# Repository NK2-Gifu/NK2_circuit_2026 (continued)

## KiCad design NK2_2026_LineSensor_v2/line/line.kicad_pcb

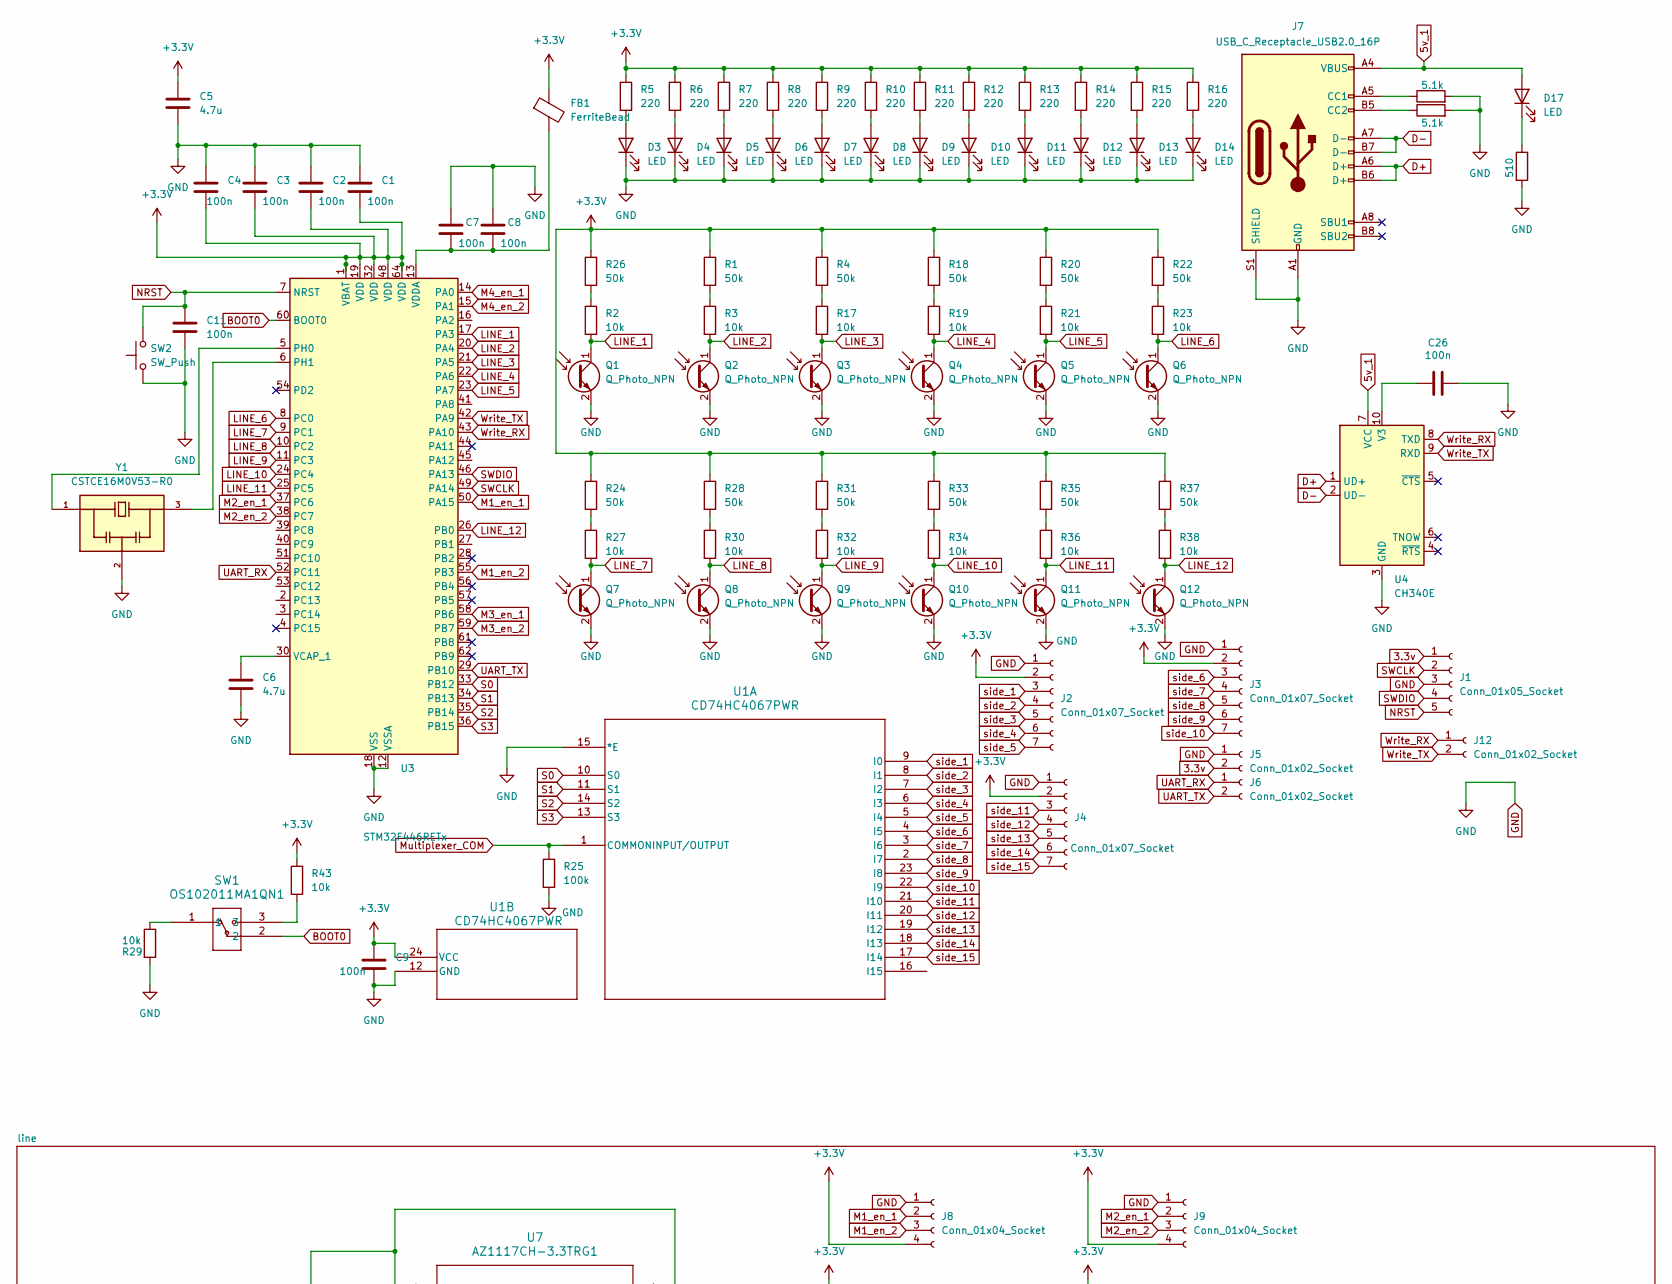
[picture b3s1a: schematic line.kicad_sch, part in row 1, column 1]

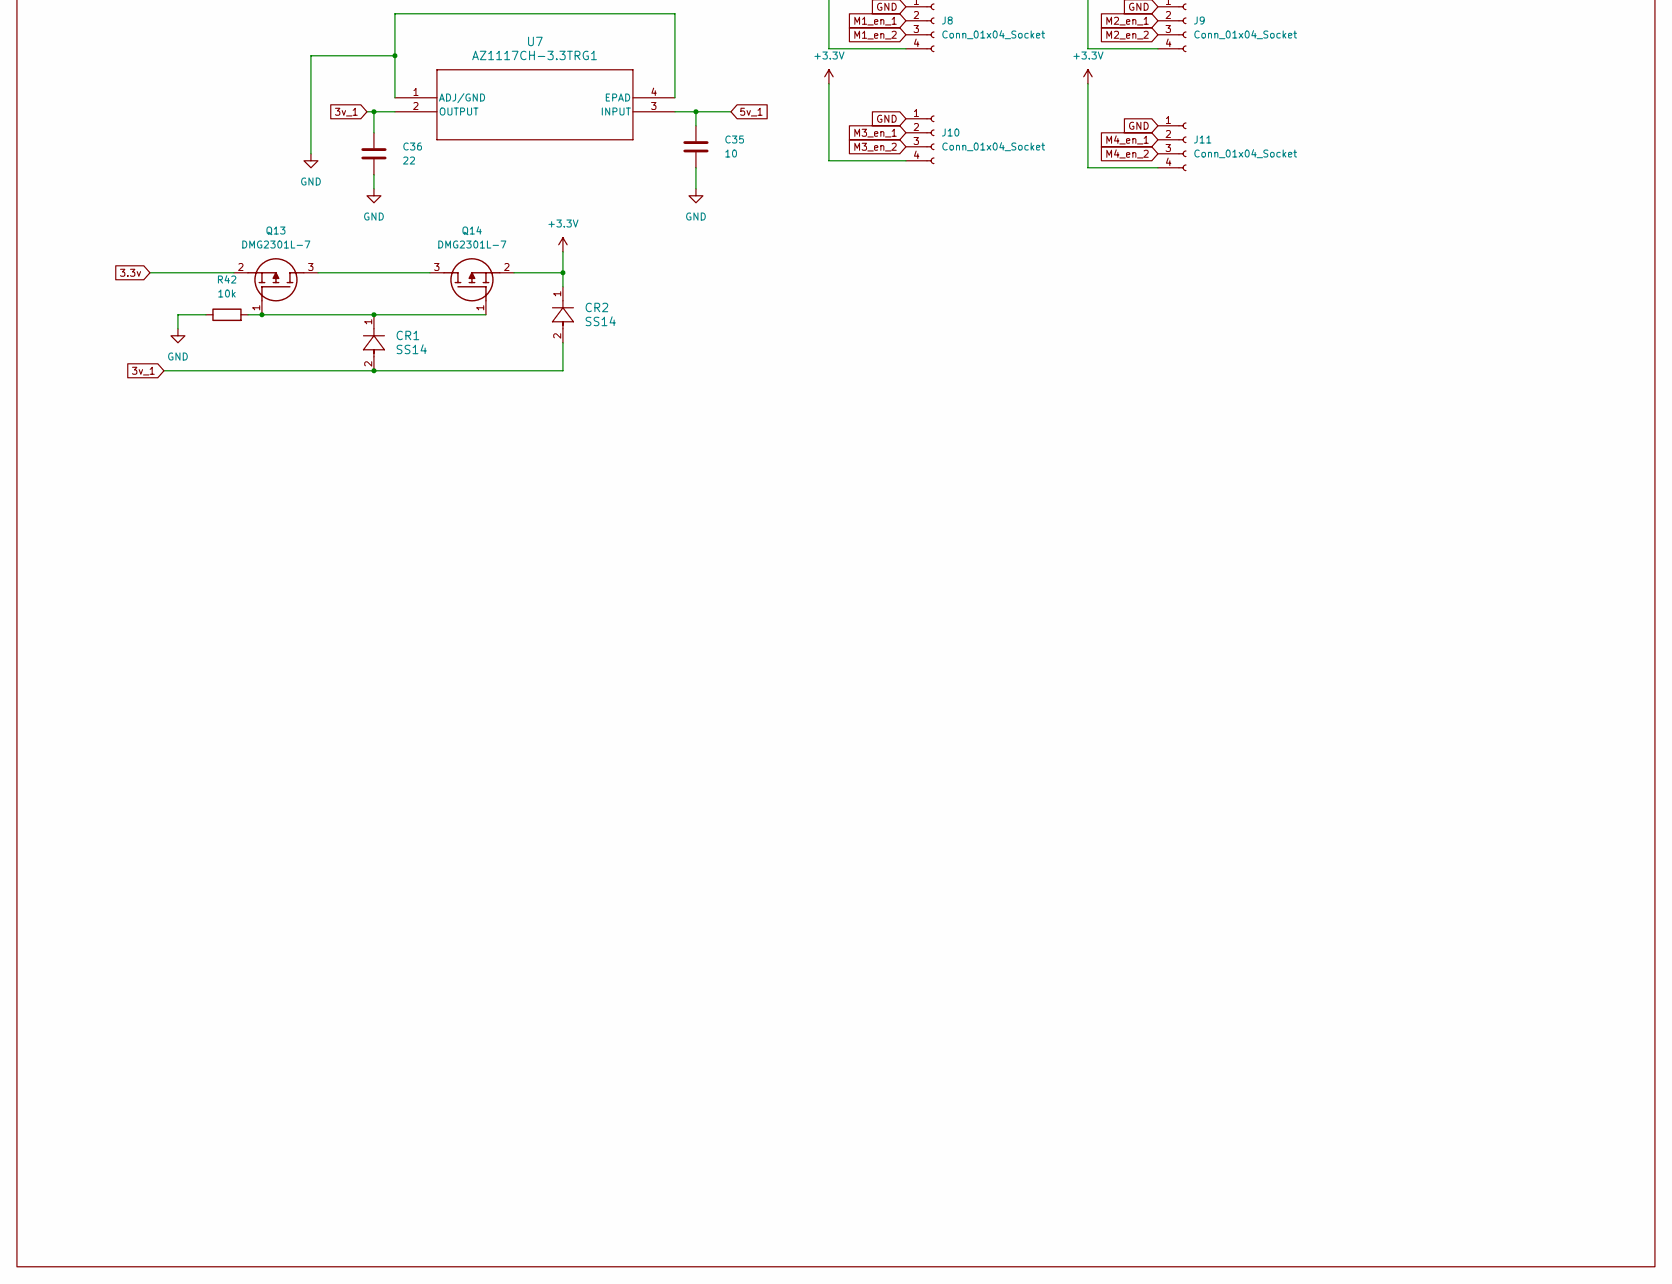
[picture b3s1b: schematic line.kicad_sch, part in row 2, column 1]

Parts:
C1, C2, C3, C4, C7, C8, C9, C11, C26: 100n; C_0402_1005Metric; LCSC C1525
C5, C6: 4.7u; C_0402_1005Metric; LCSC C23733
C35: 10; C_0603_1608Metric; LCSC C1691
C36: 22; C_1206_3216Metric; LCSC C1859
CR1, CR2: SS14; CR_SMA_403AE_OSI; LCSC C2480
D3, D4, D5, D6, D7, D8, D9, D10, D11, D12, D13, D14: LED; LED_D3.0mm_Clear
D17: LED; LED_0603_1608Metric; LCSC C2286
FB1: FerriteBead; R_0603_1608Metric; LCSC C275451
J1: Conn_01x05_Socket; JST_XH_S5B-XH-A-1_1x05_P2.50mm_Horizontal
J2, J3, J4: Conn_01x07_Socket; PinSocket_1x07_P2.54mm_Vertical
J5, J6, J12: Conn_01x02_Socket; JST_XH_B2B-XH-A_1x02_P2.50mm_Vertical
J7: USB_C_Receptacle_USB2.0_16P; USB_C_Receptacle_XKB_U262-16XN-4BVC11; LCSC C393939
J8, J9, J10, J11: Conn_01x04_Socket; JST_XH_B4B-XH-A_1x04_P2.50mm_Vertical
Q1, Q2, Q3, Q4, Q5, Q6, Q7, Q8, Q9, Q10, Q11, Q12: Q_Photo_NPN; LED_D4.0mm
Q13, Q14: DMG2301L-7; SOT96P240X115-3N; Manufacturer_Part_Number DMG2301L-7; LCSC C102619
R1, R4, R18, R20, R22, R24, R26, R28, R31, R33, R35, R37: 50k; R_0603_1608Metric
R2, R3, R17, R19, R21, R23, R27, R29, R30, R32, R34, R36, R38, R42, R43: 10k; R_0603_1608Metric
R5, R6, R7, R8, R9, R10, R11, R12, R13, R14, R15, R16: 220; R_1206_3216Metric
R25: 100k; R_0603_1608Metric
R39, R40: 5.1k; R_0603_1608Metric
R41: 510; R_0603_1608Metric
SW1: OS102011MA1QN1; OS102011MA1QN1_CNK
SW2: SW_Push; SW_PUSH_6mm_H7.3mm
U1: CD74HC4067PWR; TSSOP24_4P5X7P9_TEX; LCSC C47361296
U3: STM32F446RETx; LQFP-64_10x10mm_P0.5mm; LCSC C69336
U4: CH340E; MSOP-10_3x3mm_P0.5mm; LCSC C99652
U7: AZ1117CH-3.3TRG1; SOT-223_DIO; LCSC C92102
Y1: CSTCE16M0V53-R0; OSC_CSTCE16M0V53-R0; PARTREV 10/24/2022; LCSC C32180

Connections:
3.3v: J1.1, J5.2, Q13.2 (S)
3v_1: C36.1, CR1.2, CR2.2, U7.2 (OUTPUT)
5v_1: C35.1, D17.2 (A), J7.A4 (VBUS), J7.A9 (VBUS), J7.B4 (VBUS), J7.B9 (VBUS), U4.7 (VCC), U7.3 (INPUT)
+3.3V: C1.2, C2.2, C3.2, C4.2, C5.1, C9.1, CR2.1, FB1.1, J2.2, J3.2, J4.2, J8.4, J9.4, J10.4, J11.4, Q14.2 (S), R1.1, R4.1, R5.1, R6.1, R7.1, R8.1, R9.1, R10.1, R11.1, R12.1, R13.1, R14.1, R15.1, R16.1, R18.1, R20.1, R22.1, R24.1, R26.1, R28.1, R31.1, R33.1, R35.1, R37.1, R43.2, U1.24 (VCC), U3.1 (VBAT), U3.19 (VDD), U3.32 (VDD), U3.48 (VDD), U3.64 (VDD)
BOOT0: SW1.2, U3.60 (BOOT0)
D+: J7.A6 (D+), J7.B6 (D+), U4.1 (UD+)
D-: J7.A7 (D-), J7.B7 (D-), U4.2 (UD-)
GND: C1.1, C2.1, C3.1, C4.1, C5.2, C6.2, C7.1, C8.1, C9.2, C11.2, C26.2, C35.2, C36.2, D3.1 (K), D4.1 (K), D5.1 (K), D6.1 (K), D7.1 (K), D8.1 (K), D9.1 (K), D10.1 (K), D11.1 (K), D12.1 (K), D13.1 (K), D14.1 (K), J1.3, J2.1, J3.1, J4.1, J5.1, J7.A1 (GND), J7.A12 (GND), J7.B1 (GND), J7.B12 (GND), J7.S1 (SHIELD), J8.1, J9.1, J10.1, J11.1, Q1.2 (E), Q2.2 (E), Q3.2 (E), Q4.2 (E), Q5.2 (E), Q6.2 (E), Q7.2 (E), Q8.2 (E), Q9.2 (E), Q10.2 (E), Q11.2 (E), Q12.2 (E), R25.2, R29.2, R39.2, R40.2, R41.2, R42.1, SW2.1, U1.12 (GND), U1.15 (*E), U3.12 (VSSA), U3.18 (VSS), U3.31 (VSS), U3.47 (VSS), U3.63 (VSS), U4.3 (GND), U7.1 (ADJ/GND), U7.4 (EPAD), Y1.2
LINE_1: Q1.1 (C), R2.2, U3.17 (PA3)
LINE_2: Q2.1 (C), R3.2, U3.20 (PA4)
LINE_3: Q3.1 (C), R17.2, U3.21 (PA5)
LINE_4: Q4.1 (C), R19.2, U3.22 (PA6)
LINE_5: Q5.1 (C), R21.2, U3.23 (PA7)
LINE_6: Q6.1 (C), R23.2, U3.8 (PC0)
LINE_7: Q7.1 (C), R27.2, U3.9 (PC1)
LINE_8: Q8.1 (C), R30.2, U3.10 (PC2)
LINE_9: Q9.1 (C), R32.2, U3.11 (PC3)
LINE_10: Q10.1 (C), R34.2, U3.24 (PC4)
LINE_11: Q11.1 (C), R36.2, U3.25 (PC5)
LINE_12: Q12.1 (C), R38.2, U3.26 (PB0)
M1_en_1: J8.2, U3.50 (PA15)
M1_en_2: J8.3, U3.55 (PB3)
M2_en_1: J9.2, U3.37 (PC6)
M2_en_2: J9.3, U3.38 (PC7)
M3_en_1: J10.2, U3.58 (PB6)
M3_en_2: J10.3, U3.59 (PB7)
M4_en_1: J11.2, U3.14 (PA0)
M4_en_2: J11.3, U3.15 (PA1)
Multiplexer_COM: R25.1, U1.1 (COMMONINPUT/OUTPUT)
NRST: C11.1, J1.5, SW2.2, U3.7 (NRST)
unnamed: D3.2 (A), R5.2
unnamed: D4.2 (A), R6.2
unnamed: D5.2 (A), R7.2
unnamed: D6.2 (A), R8.2
unnamed: D7.2 (A), R9.2
unnamed: D8.2 (A), R10.2
unnamed: D9.2 (A), R11.2
unnamed: D10.2 (A), R12.2
unnamed: D11.2 (A), R13.2
unnamed: D12.2 (A), R14.2
unnamed: D13.2 (A), R15.2
unnamed: D14.2 (A), R16.2
unnamed: D17.1 (K), R41.1
unnamed: J7.A5 (CC1), R39.1
unnamed: J7.B5 (CC2), R40.1
unnamed: Q13.3 (D), Q14.3 (D)
unnamed: CR1.1, Q13.1 (G), Q14.1 (G), R42.2
unnamed: R1.2, R3.1
unnamed: R2.1, R26.2
unnamed: R4.2, R17.1
unnamed: R18.2, R19.1
unnamed: R20.2, R21.1
unnamed: R22.2, R23.1
unnamed: R24.2, R27.1
unnamed: R28.2, R30.1
unnamed: R29.1, SW1.1
unnamed: R31.2, R32.1
unnamed: R33.2, R34.1
unnamed: R35.2, R36.1
unnamed: R37.2, R38.1
unnamed: R43.1, SW1.3
unnamed: U3.5 (PH0), Y1.1
unnamed: U3.6 (PH1), Y1.3
unnamed: C6.1, U3.30 (VCAP_1)
unnamed: C7.2, C8.2, FB1.2, U3.13 (VDDA)
unnamed: C26.1, U4.10 (V3)
S0: U1.10 (S0), U3.33 (PB12)
S1: U1.11 (S1), U3.34 (PB13)
S2: U1.14 (S2), U3.35 (PB14)
S3: U1.13 (S3), U3.36 (PB15)
SWCLK: J1.2, U3.49 (PA14)
SWDIO: J1.4, U3.46 (PA13)
UART_RX: J6.1, U3.52 (PC11)
UART_TX: J6.2, U3.29 (PB10)
Write_RX: J12.1, U3.43 (PA10), U4.8 (TXD)
Write_TX: J12.2, U3.42 (PA9), U4.9 (RXD)
side_1: J2.3, U1.9 (I0)
side_2: J2.4, U1.8 (I1)
side_3: J2.5, U1.7 (I2)
side_4: J2.6, U1.6 (I3)
side_5: J2.7, U1.5 (I4)
side_6: J3.3, U1.4 (I5)
side_7: J3.4, U1.3 (I6)
side_8: J3.5, U1.2 (I7)
side_9: J3.6, U1.23 (I8)
side_10: J3.7, U1.22 (I9)
side_11: J4.3, U1.21 (I10)
side_12: J4.4, U1.20 (I11)
side_13: J4.5, U1.19 (I12)
side_14: J4.6, U1.18 (I13)
side_15: J4.7, U1.17 (I14)

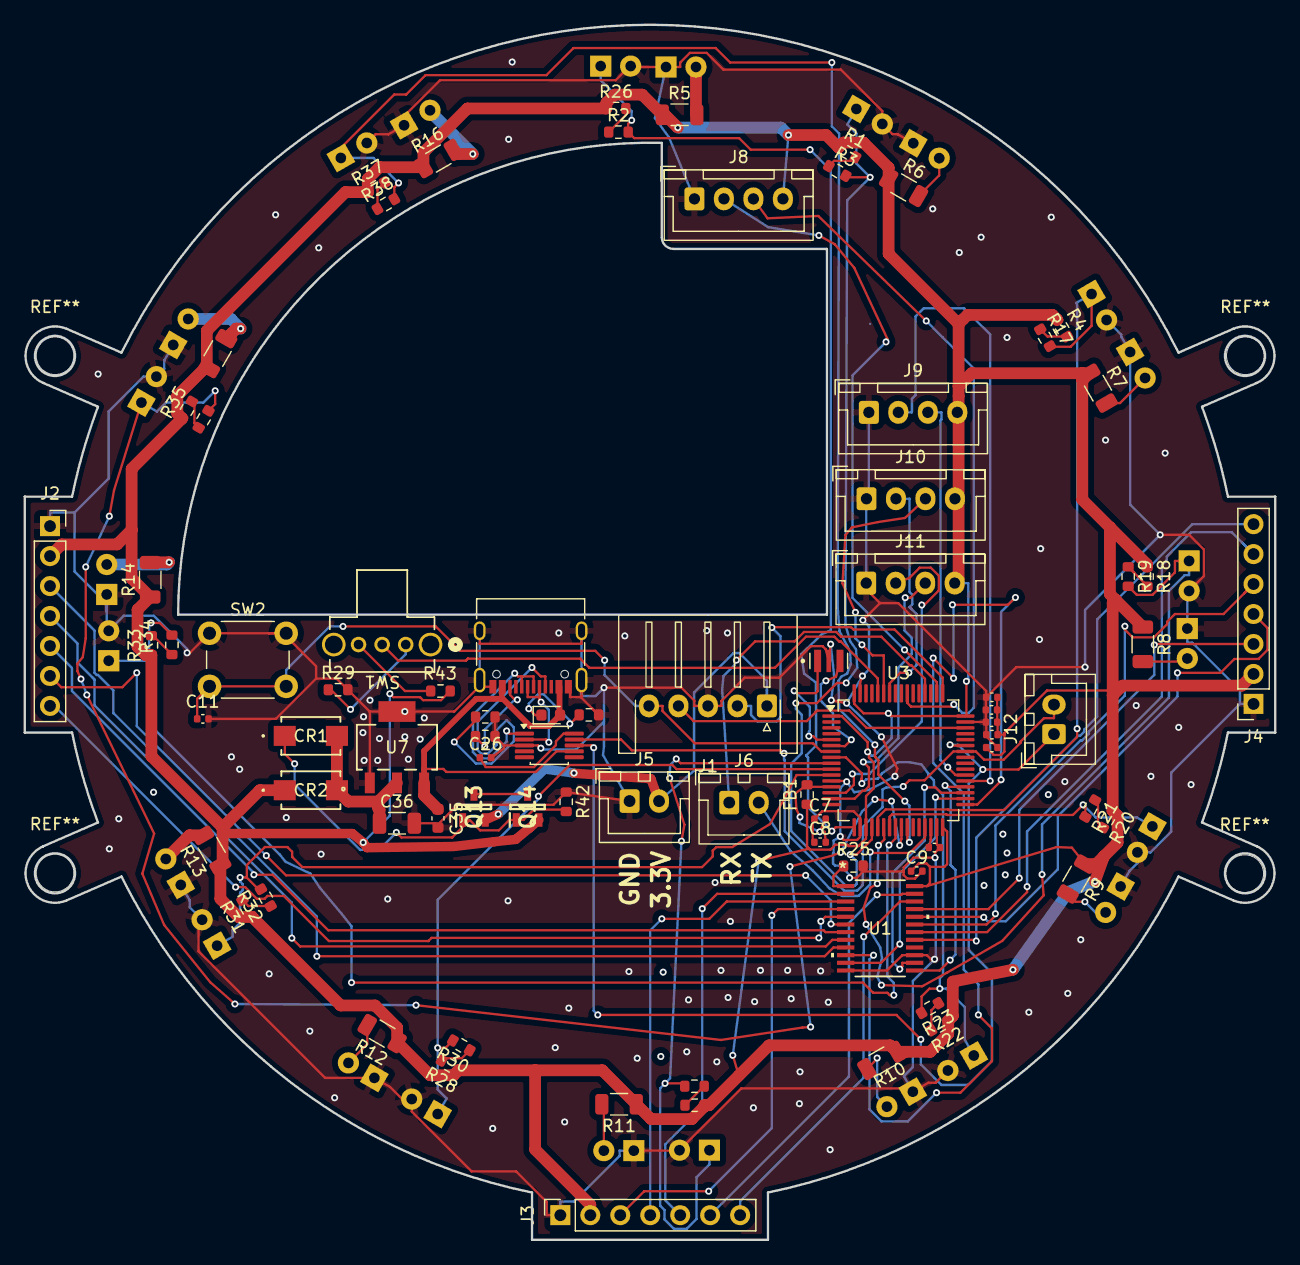
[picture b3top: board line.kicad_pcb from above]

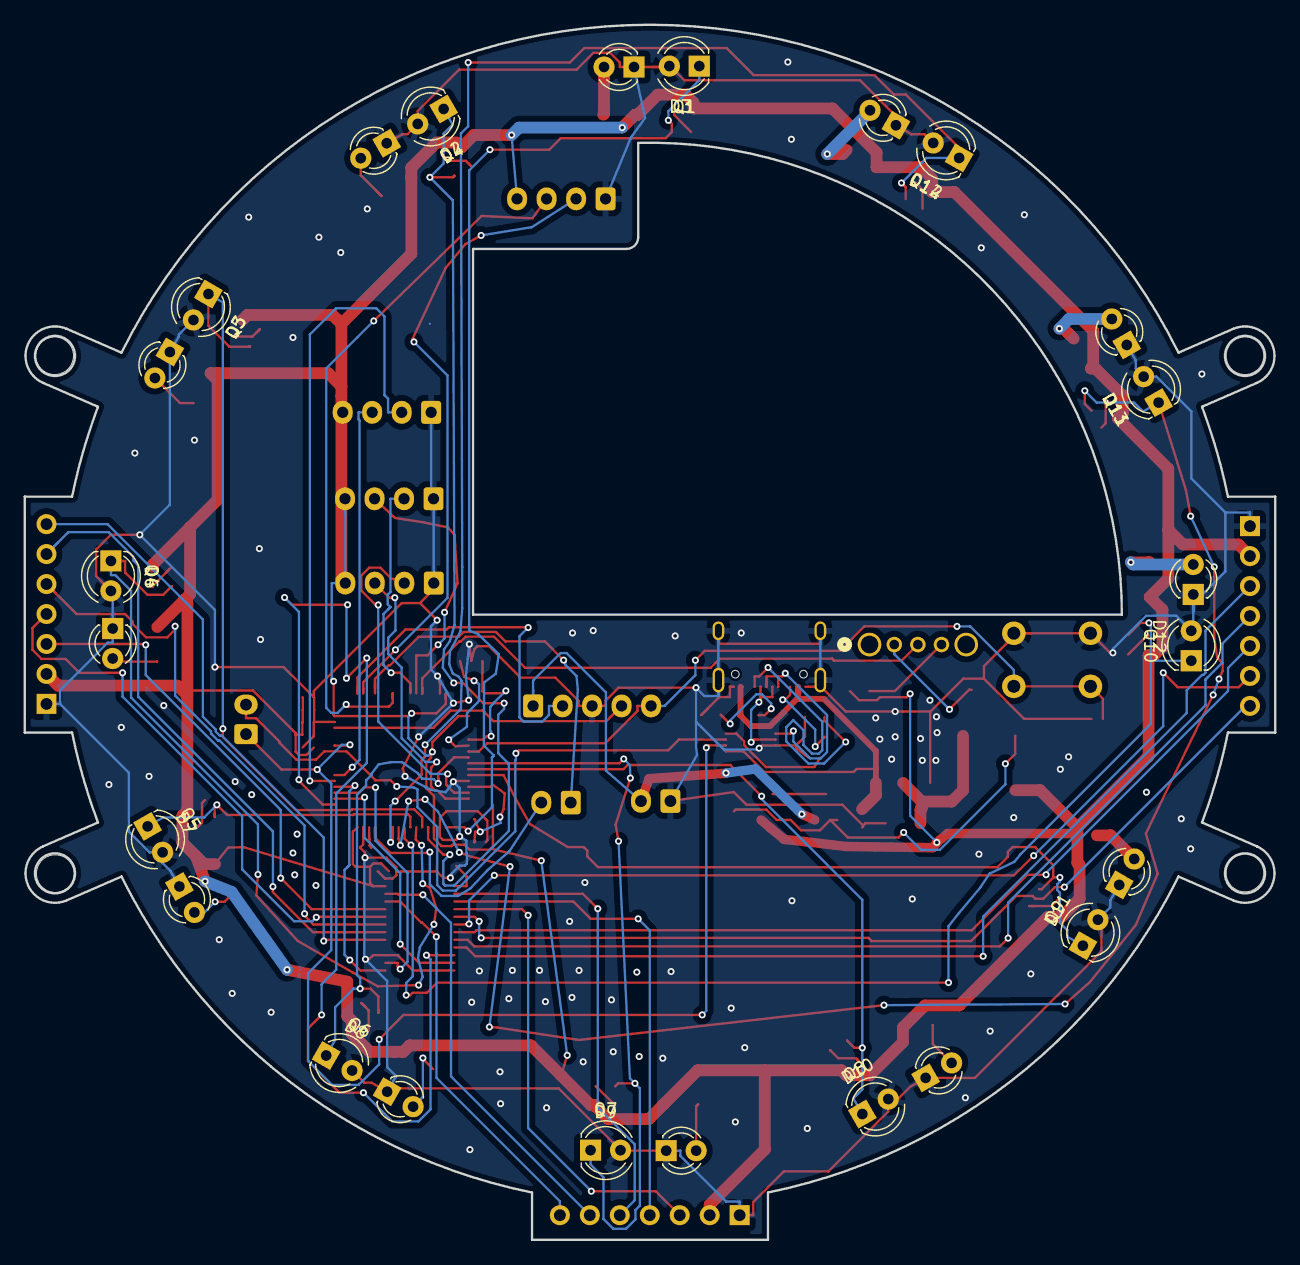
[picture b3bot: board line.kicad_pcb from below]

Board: 2 copper layers, 106.0 x 103.0 mm, 105 parts (24 on the bottom side), 91 nets.

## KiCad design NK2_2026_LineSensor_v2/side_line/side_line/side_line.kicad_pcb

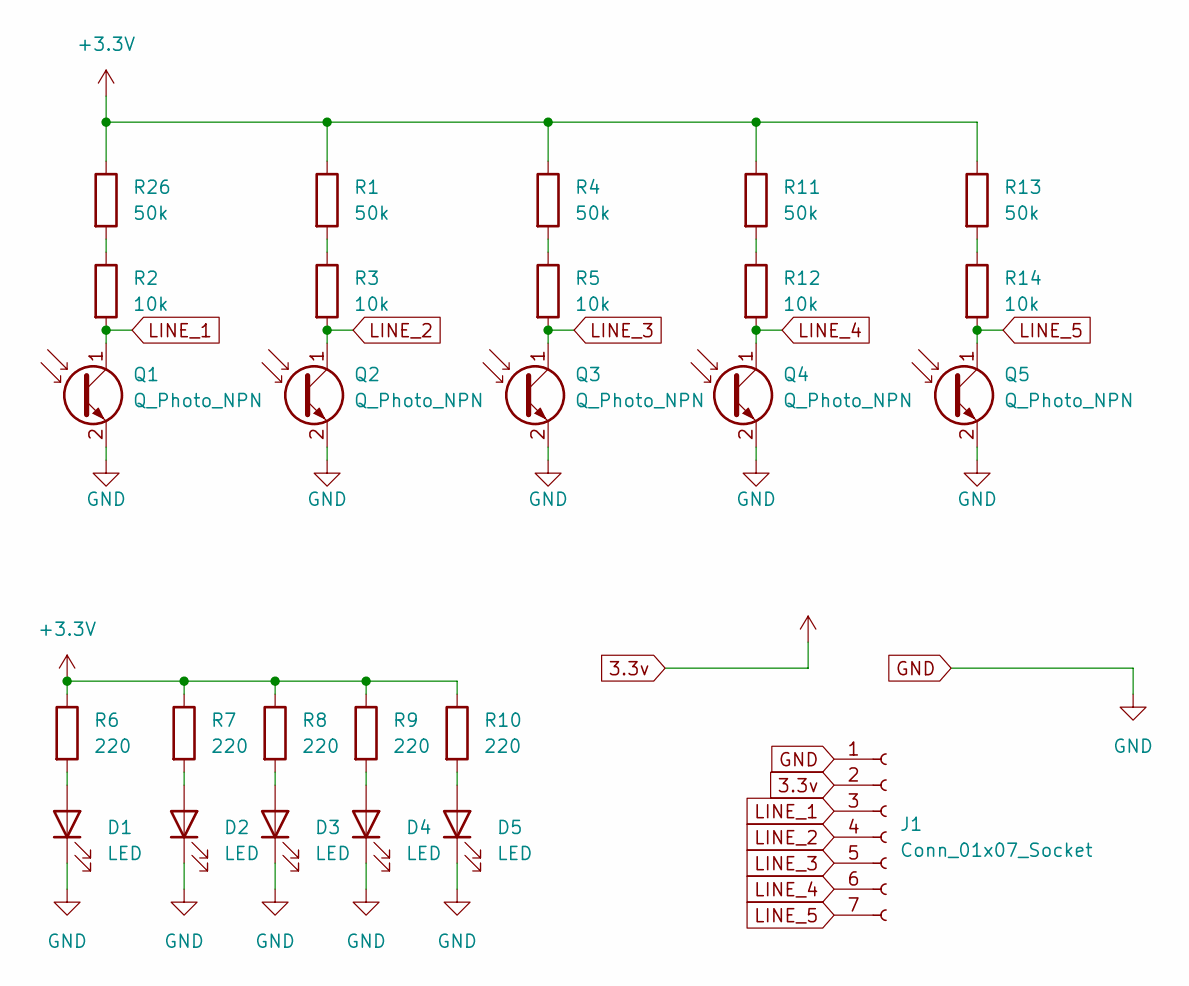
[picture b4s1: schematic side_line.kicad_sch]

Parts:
D1, D2, D3, D4, D5: LED; LED_D3.0mm_Clear
J1: Conn_01x07_Socket; PinSocket_1x07_P2.54mm_Vertical
Q1, Q2, Q3, Q4, Q5: Q_Photo_NPN; LED_D4.0mm
R1, R4, R11, R13, R26: 50k; R_0603_1608Metric; LCSC C18672
R2, R3, R5, R12, R14: 10k; R_0603_1608Metric; LCSC C15401
R6, R7, R8, R9, R10: 220; R_1206_3216Metric; LCSC C17957

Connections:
3.3v: J1.2, R1.1, R4.1, R6.1, R7.1, R8.1, R9.1, R10.1, R11.1, R13.1, R26.1
GND: D1.1 (K), D2.1 (K), D3.1 (K), D4.1 (K), D5.1 (K), J1.1, Q1.2 (E), Q2.2 (E), Q3.2 (E), Q4.2 (E), Q5.2 (E)
LINE_1: J1.3, Q1.1 (C), R2.2
LINE_2: J1.4, Q2.1 (C), R3.2
LINE_3: J1.5, Q3.1 (C), R5.2
LINE_4: J1.6, Q4.1 (C), R12.2
LINE_5: J1.7, Q5.1 (C), R14.2
unnamed: D1.2 (A), R6.2
unnamed: D2.2 (A), R7.2
unnamed: D3.2 (A), R8.2
unnamed: D4.2 (A), R9.2
unnamed: D5.2 (A), R10.2
unnamed: R1.2, R3.1
unnamed: R2.1, R26.2
unnamed: R4.2, R5.1
unnamed: R11.2, R12.1
unnamed: R13.2, R14.1

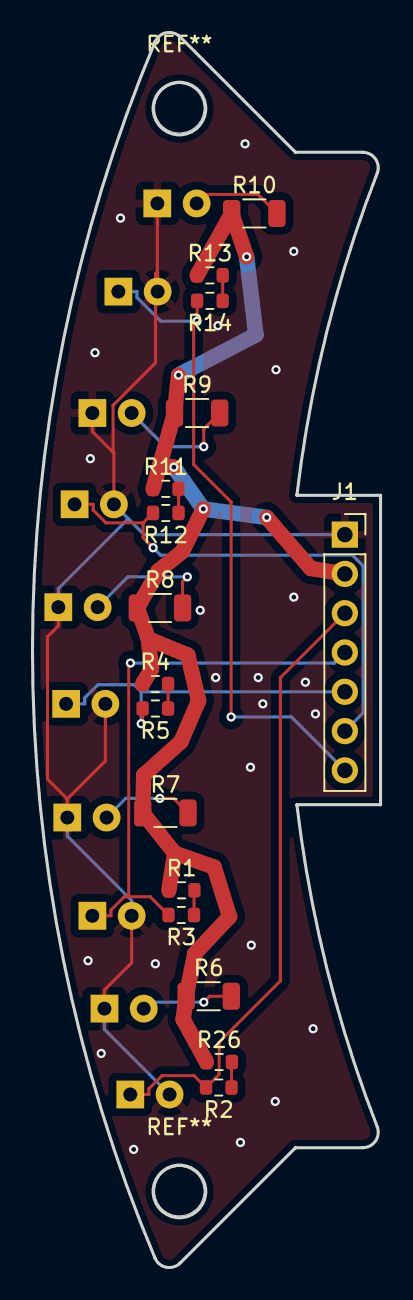
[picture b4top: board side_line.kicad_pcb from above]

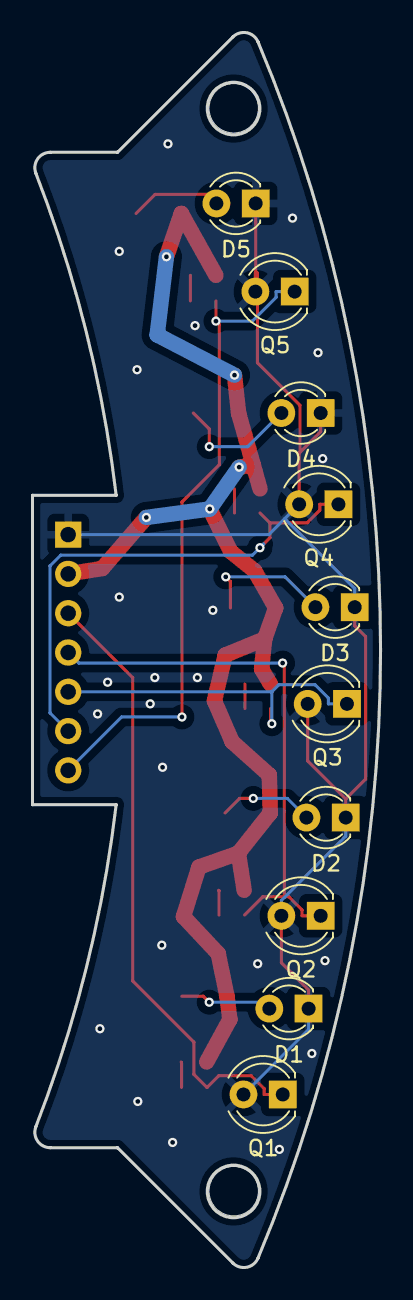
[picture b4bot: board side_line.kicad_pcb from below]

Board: 2 copper layers, 22.5 x 79.8 mm, 26 parts (10 on the bottom side), 17 nets.

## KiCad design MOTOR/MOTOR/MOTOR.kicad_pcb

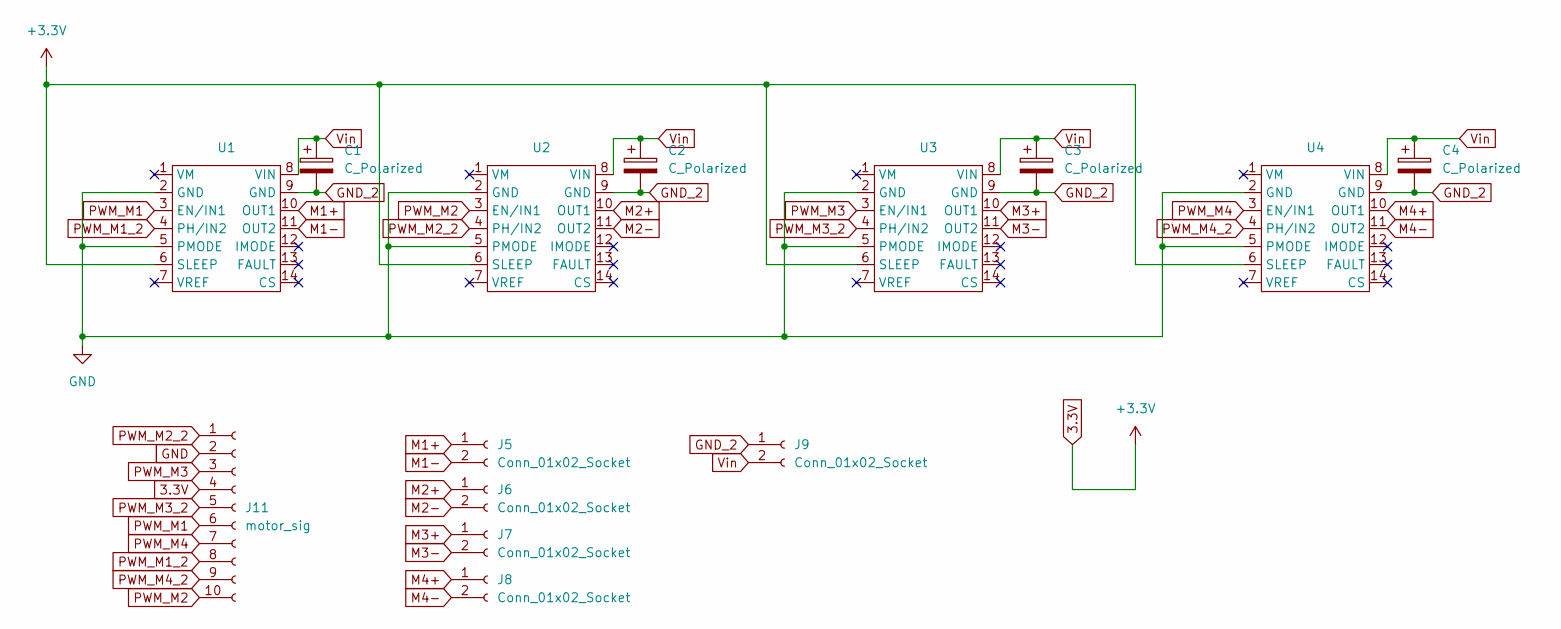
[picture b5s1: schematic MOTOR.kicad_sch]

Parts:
C1, C2, C3, C4: C_Polarized; CP_Radial_D8.0mm_P3.50mm
J5, J6, J7, J8: Conn_01x02_Socket; JST_XH_B2B-XH-A_1x02_P2.50mm_Vertical
J9: Conn_01x02_Socket; AMASS_XT30U-M_1x02_P5.0mm_Vertical
J11: motor_sig; CONN_7024610xx_MOL
U1, U2, U3, U4: drv8874

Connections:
3.3V: J11.4, U1.6 (SLEEP), U2.6 (SLEEP), U3.6 (SLEEP), U4.6 (SLEEP)
GND: J11.2, U1.2 (GND), U1.5 (PMODE), U2.2 (GND), U2.5 (PMODE), U3.2 (GND), U3.5 (PMODE), U4.2 (GND), U4.5 (PMODE)
GND_2: C1.2, C2.2, C3.2, C4.2, J9.1, U1.9 (GND), U2.9 (GND), U3.9 (GND), U4.9 (GND)
M1+: J5.1, U1.10 (OUT1)
M1-: J5.2, U1.11 (OUT2)
M2+: J6.1, U2.10 (OUT1)
M2-: J6.2, U2.11 (OUT2)
M3+: J7.1, U3.10 (OUT1)
M3-: J7.2, U3.11 (OUT2)
M4+: J8.1, U4.10 (OUT1)
M4-: J8.2, U4.11 (OUT2)
PWM_M1: J11.6, U1.3 (EN/IN1)
PWM_M1_2: J11.8, U1.4 (PH/IN2)
PWM_M2: J11.10, U2.3 (EN/IN1)
PWM_M2_2: J11.1, U2.4 (PH/IN2)
PWM_M3: J11.3, U3.3 (EN/IN1)
PWM_M3_2: J11.5, U3.4 (PH/IN2)
PWM_M4: J11.7, U4.3 (EN/IN1)
PWM_M4_2: J11.9, U4.4 (PH/IN2)
Vin: C1.1, C2.1, C3.1, C4.1, J9.2, U1.8 (VIN), U2.8 (VIN), U3.8 (VIN), U4.8 (VIN)

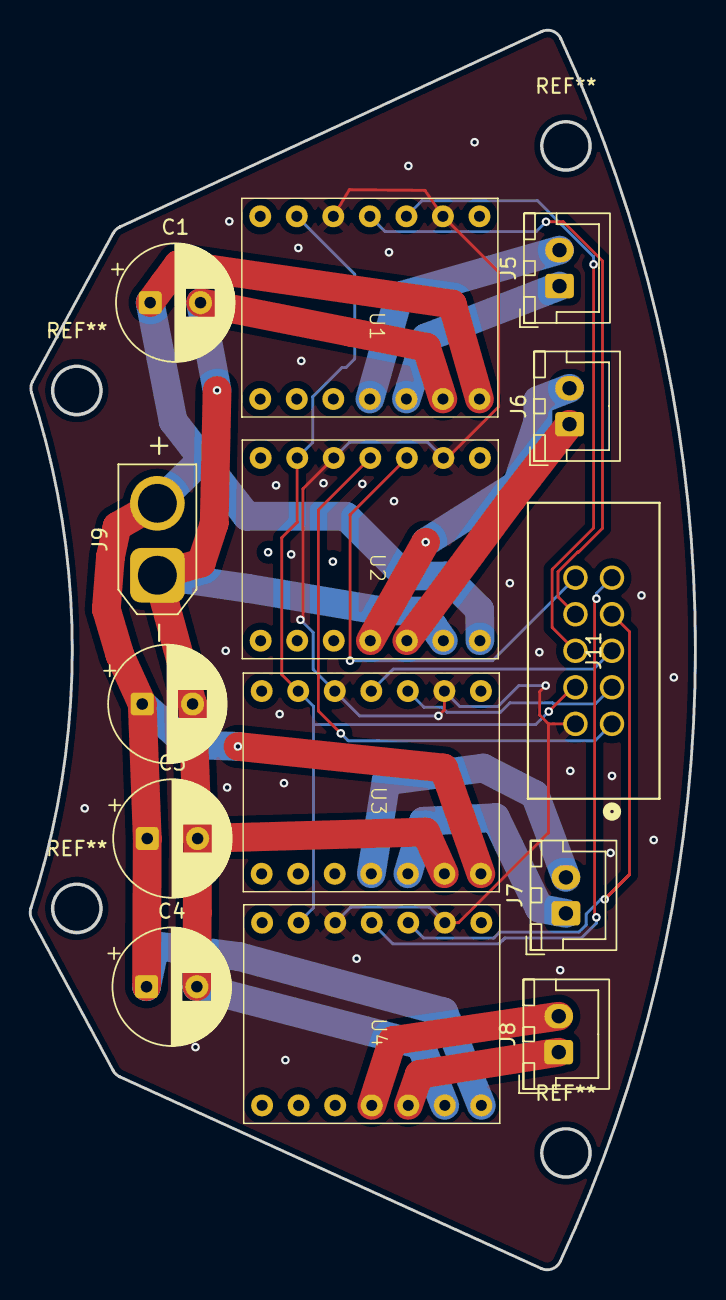
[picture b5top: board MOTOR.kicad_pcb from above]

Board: 2 copper layers, 46.2 x 86.2 mm, 14 parts (0 on the bottom side), 20 nets.

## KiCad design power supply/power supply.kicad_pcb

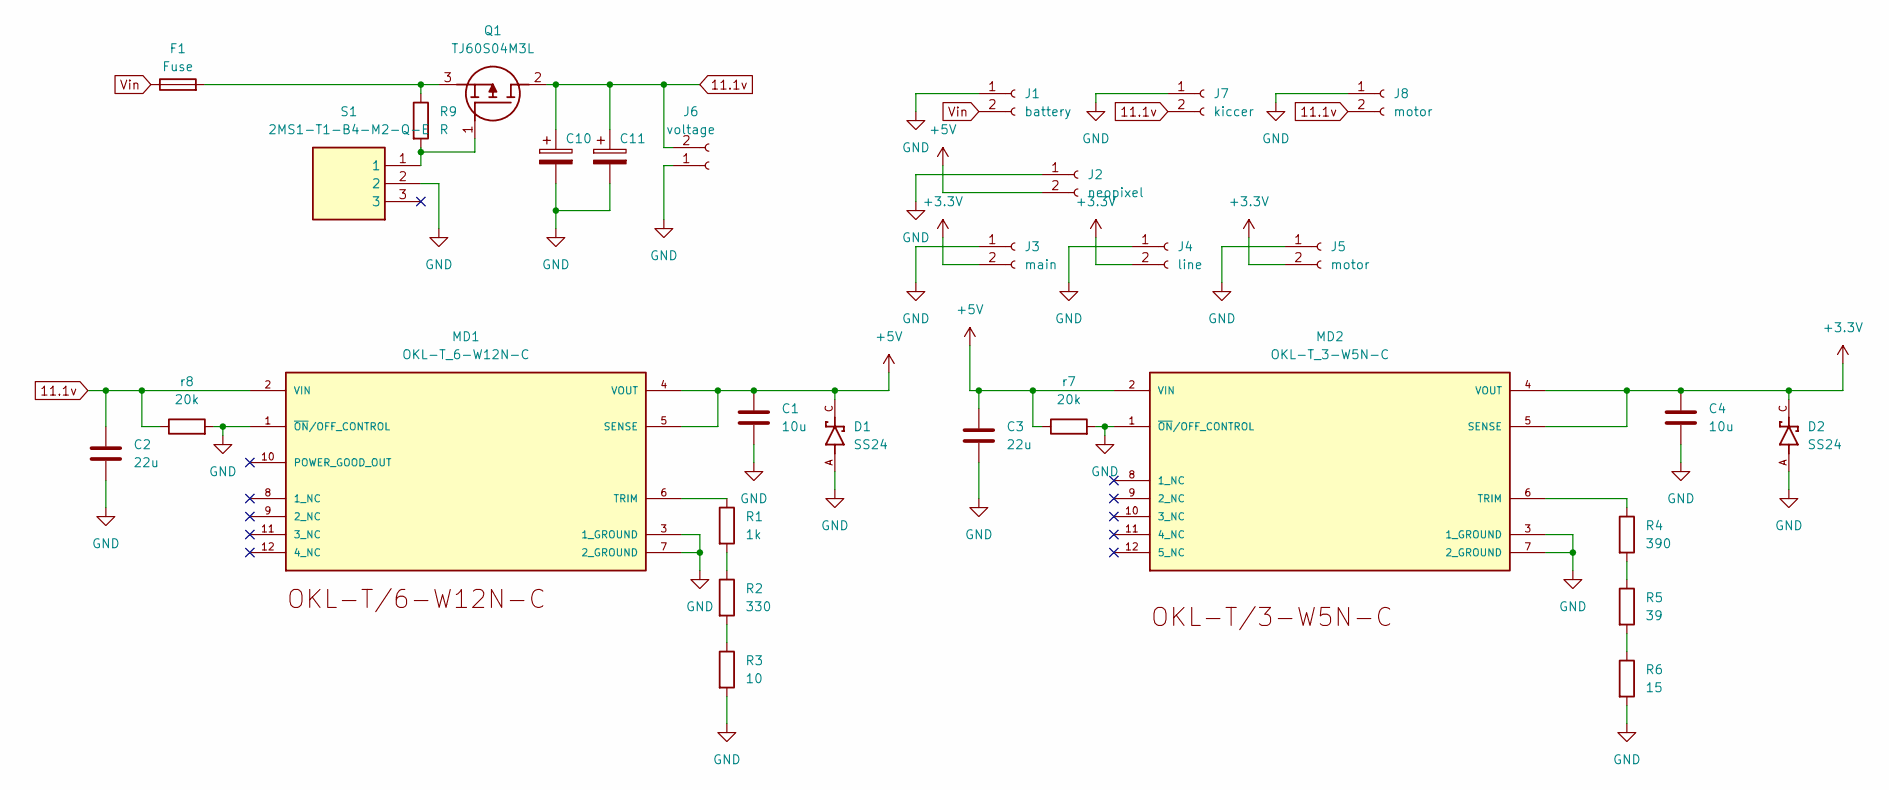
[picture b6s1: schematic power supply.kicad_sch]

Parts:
C1: 10u; C_0603_1608Metric; LCSC C1691
C2: 22u; C_1206_3216Metric; LCSC C1859
C3: 22u; C_0603_1608Metric; LCSC C1859
C4: 10u; C_1206_3216Metric; LCSC C1691
C10, C11: C_Polarized; CP_Radial_D8.0mm_P3.50mm
D1, D2: SS24; DIOM4336X265N; PARTREV N2306
F1: Fuse; Fuseholder_Clip-6.3x32mm_Littelfuse_102071_Inline_P34.70x7.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
J1: battery; AMASS_XT60-M_1x02_P7.20mm_Vertical
J2: neopixel; JST_XH_B2B-XH-A_1x02_P2.50mm_Vertical
J3: main; JST_XH_S2B-XH-A_1x02_P2.50mm_Horizontal
J4: line; JST_XH_S2B-XH-A_1x02_P2.50mm_Horizontal
J5: motor; JST_XH_S2B-XH-A_1x02_P2.50mm_Horizontal
J6: voltage; JST_XH_B2B-XH-A_1x02_P2.50mm_Vertical
J7: kiccer; JST_XH_B2B-XH-A_1x02_P2.50mm_Vertical
J8: motor; AMASS_XT30U-M_1x02_P5.0mm_Vertical
MD1: OKL-T_6-W12N-C; MURATA_OKL-T-6-W12N-C_0; MOUSER_PART_NUMBER 580-OKL-T/6-W12N-C; MOUSER_DESCRIPTION Non-Isolated DC/DC Converters 12Vin .59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
MD2: OKL-T_3-W5N-C; MURATA_OKL-T-3-W5N-C_0; MOUSER_PART_NUMBER 580-OKL-T/3-W5N-C; MOUSER_DESCRIPTION Non-Isolated 9.9 W 5 V Input 0.6 to 3.6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
Q1: TJ60S04M3L; Manufacturer_Part_Number TJ60S04M3L
R1: 1k; R_1206_3216Metric; LCSC C1469
R2: 330; R_0805_2012Metric; LCSC C17630
R3: 10; R_1206_3216Metric; LCSC C17903
R4: 390; R_1206_3216Metric; LCSC C4491
R5: 39; R_0805_2012Metric; LCSC C1324
R6: 15; R_0805_2012Metric; LCSC C17480
R9: R; R_Axial_DIN0207_L6.3mm_D2.5mm_P10.16mm_Horizontal
S1: 2MS1-T1-B4-M2-Q-E; Manufacturer_Part_Number 2MS1-T1-B4-M2-Q-E
r7, r8: 20k; R_0603_1608Metric; LCSC C4184

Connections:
11.1v: C2.1, C10.1, C11.1, J6.2, J7.2, J8.2, MD1.2 (VIN), Q1.2 (D), r8.1
+3.3V: C4.1, D2.C, J3.2, J4.2, J5.2, MD2.4 (VOUT), MD2.5 (SENSE)
+5V: C1.1, C3.1, D1.C, J2.2, MD1.4 (VOUT), MD1.5 (SENSE), MD2.2 (VIN), r7.1
GND: C1.2, C2.2, C3.2, C4.2, C10.2, C11.2, D1.A, D2.A, J1.1, J2.1, J3.1, J4.1, J5.1, J6.1, J7.1, J8.1, MD1.1 (~ON/OFF_CONTROL), MD1.3 (1_GROUND), MD1.7 (2_GROUND), MD2.1 (~ON/OFF_CONTROL), MD2.3 (1_GROUND), MD2.7 (2_GROUND), R3.2, R6.2, S1.2, r7.2, r8.2
unnamed: MD1.6 (TRIM), R1.1
unnamed: MD2.6 (TRIM), R4.1
unnamed: Q1.1 (G), R9.2, S1.1
unnamed: F1.2, Q1.3 (S), R9.1
unnamed: R1.2, R2.1
unnamed: R2.2, R3.1
unnamed: R4.2, R5.1
unnamed: R5.2, R6.1
Vin: F1.1, J1.2

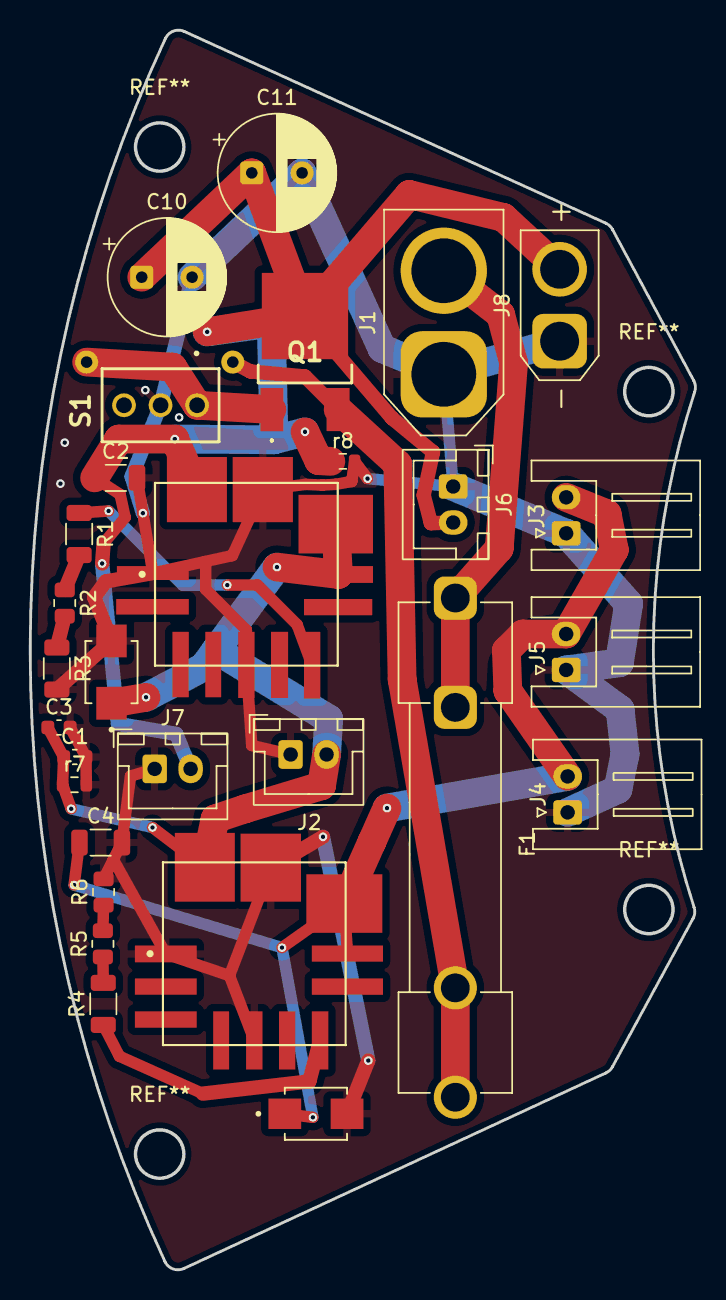
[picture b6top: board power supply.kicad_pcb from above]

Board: 2 copper layers, 46.2 x 86.2 mm, 30 parts (1 on the bottom side), 13 nets.

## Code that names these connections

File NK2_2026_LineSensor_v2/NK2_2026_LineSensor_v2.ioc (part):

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Mcu.Name=STM32F446R(C-E)Tx
Mcu.Package=LQFP64
Mcu.UserName=STM32F446RETx
PA0-WKUP.Signal=S_TIM5_CH1
PA1.Signal=S_TIM5_CH2
PA10.Mode=Asynchronous
PA10.Signal=USART1_RX
PA15.Signal=S_TIM2_CH1_ETR
PA3.Signal=ADCx_IN3
PA4.Signal=ADCx_IN4
PA5.Signal=ADCx_IN5
PA6.Signal=ADCx_IN6
PA7.Signal=ADCx_IN7
PA9.Mode=Asynchronous
PA9.Signal=USART1_TX
PB0.Signal=ADCx_IN8
PB1.Signal=ADCx_IN9
PB10.Mode=Asynchronous
PB10.Signal=USART3_TX
PB12.GPIOParameters=GPIO_Label
PB12.GPIO_Label=SIDE_S0
PB12.Signal=GPIO_Output
PB13.GPIOParameters=GPIO_Label
PB13.GPIO_Label=SIDE_S1
PB13.Signal=GPIO_Output
PB14.GPIOParameters=GPIO_Label
PB14.GPIO_Label=SIDE_S2
PB14.Signal=GPIO_Output
PB15.GPIOParameters=GPIO_Label
PB15.GPIO_Label=SIDE_S3
PB15.Signal=GPIO_Input
PB3.Signal=S_TIM2_CH2
PB6.Signal=S_TIM4_CH1
PB7.Signal=S_TIM4_CH2
PC0.Signal=ADCx_IN10
PC1.Signal=ADCx_IN11
PC11.Mode=Asynchronous
PC11.Signal=USART3_RX
PC2.Signal=ADCx_IN12
PC3.Signal=ADCx_IN13
PC4.Signal=ADCx_IN14
PC5.Signal=ADCx_IN15
PC6.Signal=S_TIM3_CH1
PC7.Signal=S_TIM3_CH2
PH0-OSC_IN.Mode=HSE-External-Oscillator
PH0-OSC_IN.Signal=RCC_OSC_IN
PH1-OSC_OUT.Mode=HSE-External-Oscillator
PH1-OSC_OUT.Signal=RCC_OSC_OUT
RCC.HSE_VALUE=16000000
RCC.SYSCLKFreq_VALUE=180000000
RCC.SYSCLKSource=RCC_SYSCLKSOURCE_PLLCLK
board=custom

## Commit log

2026-01-31 Add Main Circuit Project
2026-01-31 Add Line circuit project
2026-02-26 powersupply
    Add power supply
2026-02-26 MOTOR
    Add MOTOR
2026-02-26 kiccker
    Add kiccker
2026-02-26 コネクタの位置を変えた
2026-03-16 main and ball
    更新した
2026-04-06 kicker
